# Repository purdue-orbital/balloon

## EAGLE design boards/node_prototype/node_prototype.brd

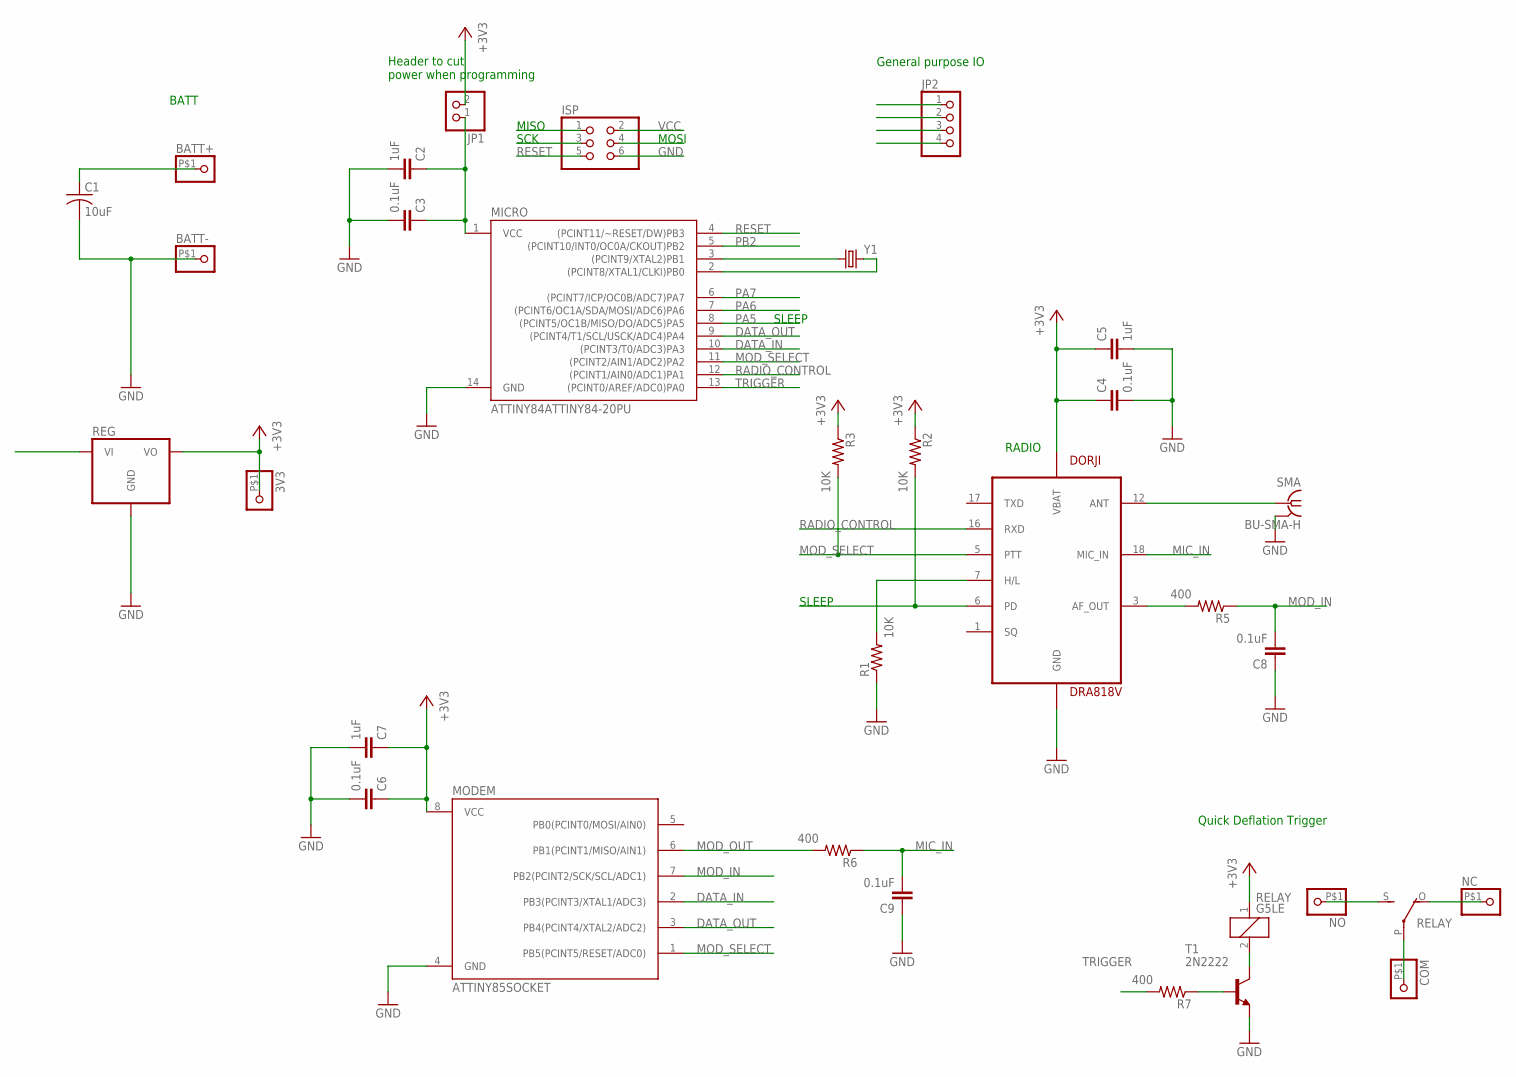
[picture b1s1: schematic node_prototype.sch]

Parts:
3V3: PINHD-1X1; 1X01
BATT+: PINHD-1X1; 1X01
BATT-: PINHD-1X1; 1X01
C1: 10uF; C025-050X050
C2, C5, C7: 1uF; C0603
C3, C4, C6, C8, C9: 0.1uF; C0603
COM: PINHD-1X1; 1X01
DORJI: DRA818V; DORJI
ISP: PINHD-2X3; 2X03
JP1: PINHD-1X2; 1X02
JP2: PINHD-1X4; 1X04
MICRO: ATTINY84ATTINY84-20PU; DIL14
MODEM: ATTINY85SOCKET; SOCKET-08
NC: PINHD-1X1; 1X01
NO: PINHD-1X1; 1X01
R1, R2, R3: 10K; R0603
R5, R6, R7: 400; R0603
REG: AP1117-3.3SOT223; SOT223
RELAY: G5LE
SMA: BU-SMA-H
T1: 2N2222; TO18
Y1: CRYSTAL; MYSMD2_RESONATOR

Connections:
+3V3: 3V3.P$1, C4.1, C5.1, C6.1, C7.1, DORJI.8 (VBAT), JP1.2, MODEM.8 (VCC), R2.1, R3.1, REG.2 (VO), REG.4 (VO), RELAY.1
BATT: BATT+.P$1, C1.1, REG.3 (VI)
DATA_IN: MICRO.10 ((PCINT3/T0/ADC3)PA3), MODEM.2 (PB3(PCINT3/XTAL1/ADC3))
DATA_OUT: ISP.3, MICRO.9 ((PCINT4/T1/SCL/USCK/ADC4)PA4), MODEM.3 (PB4(PCINT4/XTAL2/ADC2))
GND: BATT-.P$1, C1.2, C2.2, C3.2, C4.2, C5.2, C6.2, C7.2, C8.1, C9.1, DORJI.9 (GND), DORJI.10 (GND), ISP.6, MICRO.14 (GND), MODEM.4 (GND), R1.1, REG.1 (GND), SMA.2, SMA.3 (2), SMA.4 (2), SMA.5 (2), T1.1 (E)
MIC_IN: C9.2, DORJI.18 (MIC_IN), R6.1
MOD_IN: C8.2, MODEM.7 (PB2(PCINT2/SCK/SCL/ADC1)), R5.1
MOD_OUT: MODEM.6 (PB1(PCINT1/MISO/AIN1)), R6.2
MOD_SELECT: DORJI.5 (PTT), MICRO.11 ((PCINT2/AIN1/ADC2)PA2), MODEM.1 (PB5(PCINT5/RESET/ADC0)), R3.2
unnamed: DORJI.12 (ANT), SMA.1
unnamed: DORJI.7 (H/L), R1.2
unnamed: DORJI.3 (AF_OUT), R5.2
unnamed: R7.1, T1.2 (B)
unnamed: RELAY.2, T1.3 (C)
unnamed: MICRO.3 ((PCINT9/XTAL2)PB1), Y1.1
unnamed: NO.P$1, RELAY.S
unnamed: NC.P$1, RELAY.O
unnamed: COM.P$1, RELAY.P
unnamed: MICRO.2 ((PCINT8/XTAL1/CLKI)PB0), Y1.3 (2)
PA5: DORJI.6 (PD), ISP.1, JP2.4, MICRO.8 ((PCINT5/OC1B/MISO/DO/ADC5)PA5), R2.2
PA6: ISP.4, JP2.3, MICRO.7 ((PCINT6/OC1A/SDA/MOSI/ADC6)PA6)
PA7: JP2.2, MICRO.6 ((PCINT7/ICP/OC0B/ADC7)PA7)
PB2: JP2.1, MICRO.5 ((PCINT10/INT0/OC0A/CKOUT)PB2)
RADIO_CONTROL: DORJI.16 (RXD), MICRO.12 ((PCINT1/AIN0/ADC1)PA1)
RESET: ISP.5, MICRO.4 ((PCINT11/~RESET/DW)PB3)
TRIGGER: MICRO.13 ((PCINT0/AREF/ADC0)PA0), R7.2
VCC: C2.1, C3.1, ISP.2, JP1.1, MICRO.1 (VCC)

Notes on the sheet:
RADIO
BATT
SCK
MISO
MOSI
SLEEP
Header to cut power when programming
General purpose IO
Quick Deflation Trigger

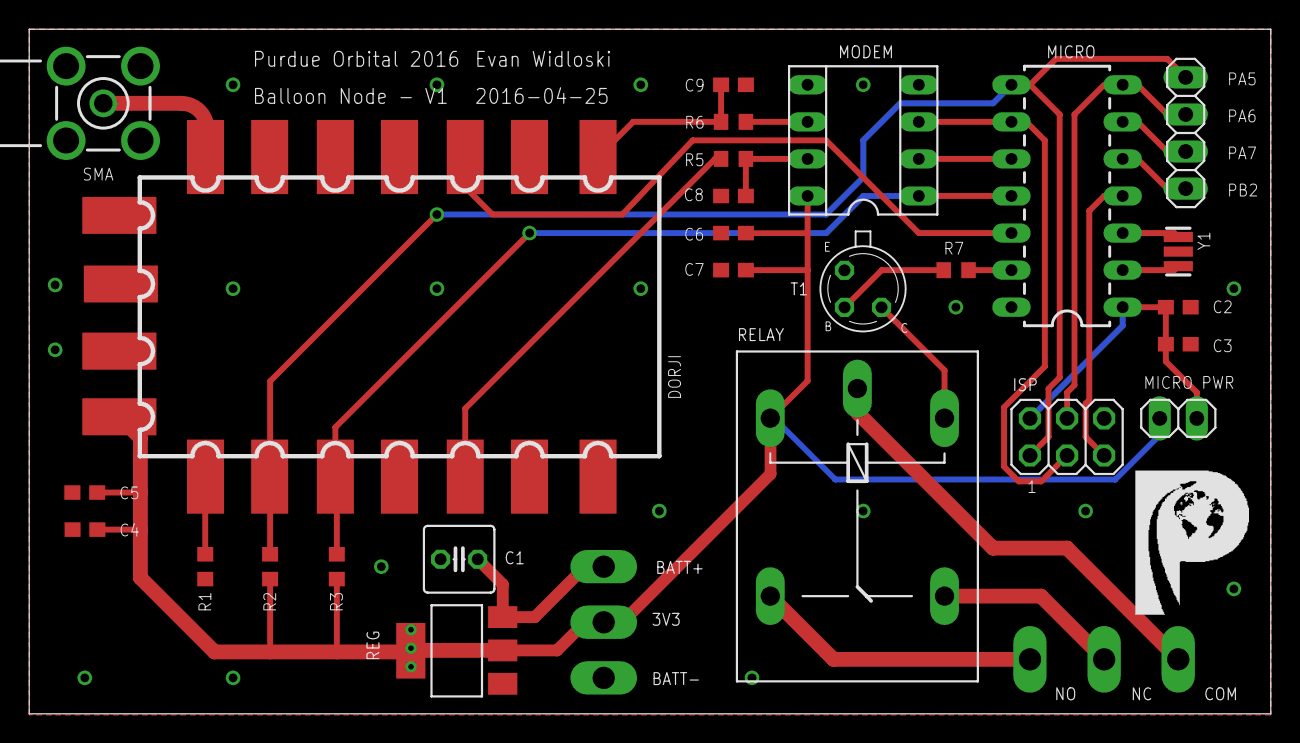
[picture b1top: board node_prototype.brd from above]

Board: 2 copper layers, 85.1 x 46.9 mm, 32 parts (0 on the bottom side), 27 nets.

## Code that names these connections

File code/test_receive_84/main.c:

/* Evan Widloski - 2016-09-21

   Pinout
   ------
         ATTiny84
          ------
   VCC  --|o   |--  GND
   PB0  --|    |--  PA0 - RELAY
   PB1  --|    |--  PA1
   PB3  --|    |--  PA2 - Radio TX/RX (TX = 0)
   PB2  --|    |--  PA3 - TX
   PA7  --|    |--  PA4 - RX
   PA6  --|    |--  PA5
          ------
*/

#include <avr/io.h>
#include <avr/interrupt.h>
#include <util/delay.h>
//
// A simple program for the ATtiny84 that blinks an LED.
//
// electronut.in
//

#include <avr/io.h>
#include <util/delay.h>
 
#define F_CPU 8000000

int main (void)
{
  DDRA = (1 << PA0) | (1 << PA2) | (1 << PA3);

  // turn off radio
  PORTA |= (1 << PA2);

  while (1) {

    if (PINA & (1 << PA4)){
      PORTA |= (1 << PA0);
    }
    else {
      PORTA &= ~(1 << PA0);
    }
  }
  return 1;
}

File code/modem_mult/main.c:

/* Evan Widloski - 2016-03-25
   Bell202 Modem for ATTiny85

   Adapted from https://sites.google.com/site/wayneholder/attiny-4-5-9-10-assembly-ide-and-programmer/bell-202-1200-baud-demodulator-in-an-attiny10

   Pinout
   ------
                      ATTiny85
                       ------
   mod select  PB5   --|o   |--
   data in     PB3   --|    |--   PB2  mod in
   data out    PB4   --|    |--   PB1  mod out
                     --|    |--
                       ------
*/

#include <avr/io.h>
#include <avr/interrupt.h>
#include <util/delay.h>


uint8_t ADC_READY = 0;

int8_t samples[8] = {0,0,0,0,0,0,0,0};

int main()
{

  // --- Data pin Init ---
  // Set pullup on data in and mod select
  PORTB |= 1<<PB5 | 1<<PB3;

  // --- Demodulation Init ---
  //enable data out
  DDRB |= 1<<DDB4;

  // Set Timer 0 prescaler to 8
  TCCR0B = 1<<CS01;
  // Put Timer 0 in CTC mode (reset at OCR0A)
  TCCR0A = 1<<WGM01;
  // Sample at 9600Hz on 8MHz clock with 8x prescaler
  // (8000000/8)/9600 = 104.17
	OCR0A = 104;

	//Result Left Justified, channel ADC1
	ADMUX = (1<<ADLAR)|(1<<MUX0);
  // Enable ADC, enable ADC auto triggering
  ADCSRA = 1<<ADEN | 1<<ADATE;
  // Trigger ADC on Timer0 Compare Match A
  ADCSRB = 1<<ADTS1 | 1<<ADTS0;

  //start ADC
  ADCSRA |= 1<<ADSC;

  // --- Modulation Init ---

  // enable mod out
  DDRB |= 1<<DDB1;

  // enable toggling of OC1A
  TCCR1 |= 1<<COM1A0;
  // unmask data-in interrupt pin
  PCMSK |= 1<<PCINT3;

  // Put Timer 1 in CTC mode, Set Timer 1 Prescaler to 16
  TCCR1 |= 1<<CTC1 | 1<<CS12 | 1<<CS10;

  // interrupt on OCR1A match
  TIMSK |= 1<<OCIE1A;

  //enable global interrupts
	sei();

  int16_t out = 0;

  uint8_t oldest_sample = 0;

  int16_t dtft_1200_real, dtft_1200_imag, dtft_2200_real, dtft_2200_imag;
  // define coefficient vectors
  int8_t coeff_1200_real[8] = {127,   90,    0,  -90, -127,  -90,    0,   90};
  int8_t coeff_1200_imag[8] = {  0,  -90, -127,  -90,    0,   90,  127,   90};
  int8_t coeff_2200_real[8] = {127,   16, -123,  -49,  110,   77,  -90, -101};
  int8_t coeff_2200_imag[8] = {  0, -126,  -33,  117,   63, -101,  -90,   77};

	while(1) {

    // check if ADC ready
    if (ADCSRA & 1<<ADIF){

      // reset the Timer 0 Compare Match A flag
      TIFR = 1<<OCF0A;

      // clear ADC flag
      ADCSRA |= 1<<ADIF;

      // add most recent ADC reading to samples[]
      /* samples[oldest_sample] = (int8_t)ADCH - 127; */
      samples[oldest_sample] = (int8_t)ADCH - 127;
      oldest_sample = (oldest_sample + 1) % 8;


      dtft_1200_real =  dtft_1200_imag =  dtft_2200_real =  dtft_2200_imag = 0;

      for (int i = 0; i < 8; i++){
        dtft_1200_real += (int8_t)(((int16_t)samples[(oldest_sample + i) % 8]*(int16_t)coeff_1200_real[(oldest_sample + i) % 8])>>7);
        dtft_1200_imag += (int8_t)(((int16_t)samples[(oldest_sample + i) % 8]*(int16_t)coeff_1200_imag[(oldest_sample + i) % 8])>>7);
        dtft_2200_real += (int8_t)(((int16_t)samples[(oldest_sample + i) % 8]*(int16_t)coeff_2200_real[(oldest_sample + i) % 8])>>7);
        dtft_2200_imag += (int8_t)(((int16_t)samples[(oldest_sample + i) % 8]*(int16_t)coeff_2200_imag[(oldest_sample + i) % 8])>>7);
      }
      dtft_1200_real = dtft_1200_real>>3;
      dtft_1200_imag = dtft_1200_imag>>3;
      dtft_2200_real = dtft_2200_real>>3;
      dtft_2200_imag = dtft_2200_imag>>3;

      int16_t dtft_1200 = dtft_1200_real*dtft_1200_real +
        dtft_1200_imag*dtft_1200_imag;
      int16_t dtft_2200 = dtft_2200_real*dtft_2200_real +
        dtft_2200_imag*dtft_2200_imag;

      out = dtft_2200;

      /* out = (int16_t)dtft_1200_real*(int16_t)dtft_1200_real; */

      //2200Hz detected, set output high
      if (out > 500){
        PORTB |= 1<<PB4;
      }

      // 1200Hz detected, set output low
      /* else if (out < 0){ */
      else{
        PORTB &= ~(1<<PB4);
      }
    }
  }
}


ISR(TIMER1_COMPA_vect){
  if (PINB & 1<<PB3){
    // ((8000000/16)/2200)/2 = 113.64
    OCR1A = OCR1C = 113;
  }
  // if logic 0 input, modulate 1200Hz
  else {
    // ((8000000/16)/1200)/2 = 208.33
    OCR1A = OCR1C = 207;
  }
}

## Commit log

2016-02-03 init comimt
2016-02-03 init commit dos
2016-02-03 moving to new repo
2016-02-06 ayy lmao
2016-02-06 add attiny build files
2016-02-13 add timer test code
2016-02-13 add gitignore for code
2016-02-13 added bell202 modulation test
2016-02-17 add pulse modulation test
2016-02-17 add pointless simulation files
2016-02-27 add test code for modulation, demodulation and communication with main micro
2016-02-29 began work on complete modem code
2016-03-02 completed modem testing
2016-03-02 update board with correct modem pinout
2016-03-03 Adding Kevin's code
    Code for packet generation
2016-03-04 add micro
2016-03-06 Added files via upload
2016-03-07 added shopping list
2016-03-11 Added arduino master and slave code. WDT included but no timeouts yet.
2016-03-23 i dont even know what i updated
2016-03-26 working demodulator
2016-04-01 completed modem
2016-04-01 add computation and simulation code
2016-04-01 update shopping list
2016-04-01 update shop
2016-04-02 renamed slave node, update shopping
2016-04-10 update simulations
2016-04-14 finish dumb node, update sims
2016-04-23 use attiny84
2016-04-25 update rocketradio board, complete
2016-04-25 rename rocket radio, add renders
2016-12-12 reorganize code dir
2017-02-19 Update master_nano.ino
    At first the arduinos appeared to stop sending serial data soon after beginning communication. Increasing baud rate of the serial between the two microcontrollers and controlling how often commands a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
    Fundamental changes to the protocol were made as well. The boards are now referred to as board 1 and board 2. They are differentiated from one another in software by reading the analog voltage input 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
2017-04-02 local code tests
2017-04-02 added displayfunction
    Added in displayfunction and file writing
2017-04-05 one way communication with attention pin working
2017-04-09 Buffer Update to UI_Arduino
    Made some changes to buffer. Now waiting for protocol implementation that will fill in the for and while loop conditions.
2017-04-09 full duplex with attention pin partially working
2017-04-09 Added Parsing of RX Data
    RX data is now parsed through parseRxData() which takes data from rxBuff[]. Still need to integrate buffer and duplex spi code.
2017-04-09 changed if and while structures in talk
2017-04-09 beggining some integration
2017-04-12 Small Update to the To Do List
2017-04-12 Update UI_Arduino.c
    *** Created the following cases for Act On User: go and stop (for control of 1st DOF)
    *** Filled in loop() function so that arduino waits for input of % followed by command character, then calls talk() if there is data to send or receive
    *** talk() command now calls parseRxData before returning, if there is rxData in buffer to process rx data. NOTE: May interrupt user command inputs
    *** Set ATTENTION_OUT high after every end of transmission stream in talk(). This assumes the buffer will always be completely emptied in talk(). Every time addTxBuff() is called, the ATTENTION_OUT p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
    *** Flaw in parseRxData requires transmission of '@' at end of every trans
2017-04-12 partial slave code conversion
2017-04-12 partial master code switch-over
2017-04-12 more changes
2017-04-13 Updated parseRxData()
    Following updates to parseRxData()
    *** Fixed flaw where '@' was required at end of stream of incoming data for data to be parsed properly. '@' can now be used purely as a start delimeter (can also represent data as they could in the p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
    *** parseRxData() no longer requires the entire packets to be added to the rxBuff[]. parseRxData() will now automatically shift and save a partial packet if one is encountered at the end of the logic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
    *** parseRxData() should now be ok with interrupts occurring during it's execution. Any new data added during the execution of parseRxData() is ignored. The lines of code that shift the data in the rx
2017-04-15 Updated & Tested writeData
    *** writeData now uses the legacy Tx request frame type
    *** writeData accepts a variable payload in the form of an array and requires length of payload as the 2nd parameter.
    *** TESTED writeData, success!
2017-04-15 Receiving Functions Update and Test
    ***defines were updated, and a method of testing receiving of radio packets was placed , commented out, in void loop()
    ***radRxBuff and supporting functions created for data coming in from radio, ardTxBuff and supporting functions created for data being sent to arduino (only TESTED radRxBuff & supporting functions)
    ***Replaced extractRadPackets with parseRadData and TESTED, however..... WARNING: PAYLOADS OF 6 BYTES DO NOT WORK FOR SOME REASON, NOT SURE IF THE ISSUE IS SENDING OR RECEVING, FOR NOW PAYLOAD WILL B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
    ***Added printArray to quickly debug future problems by passing printArray the address of the first array element to be printed and the
2017-04-15 writeData
    updated writeData() to most recently tested version.... may not have actually changed anything
